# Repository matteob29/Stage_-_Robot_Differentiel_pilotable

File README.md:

# Stage - Robot Différentiel pilotable

Projet réalisé dans le cadre du **Stage de Première année**

**Ateliers destinés aux stagiaires de seconde**  
**ENSEIRB-MATMECA – CEA** 

**Auteurs :**  
Mattéo BINET  
Bastien TRAN-RUESCHE 

**Encadrant :**  
Thierry TARIS

**Date :** Juin 2025  

---

## Présentation générale

Cet atelier a été conçu dans le cadre du partenariat entre **l’ENSEIRB-MATMECA** et le **CEA**, dans le but d’initier des élèves de seconde aux bases de la robotique.  
Il s’est déroulé à **EirLab**, le fablab de l’enseirb, sur des séances de trois heures encadrées par des étudiants de première année.

L’objectif était de faire découvrir la démarche complète de conception d’un système embarqué à travers la réalisation d’un **robot différentiel pilotable**.  
L’atelier combine ainsi trois volets :  
1. la **découverte du robot et de ses composants** ;  
2. la **fabrication partielle du châssis** et l’assemblage ;  
3. la **programmation du comportement autonome** du robot.

---

## Le robot

Le robot conçu est un **modèle différentiel** à deux roues motrices et une roue folle.  
Chaque moteur est commandé indépendamment à l’aide d’un **driver L298**, piloté par un **microcontrôleur ESP32** programmé dans l’environnement Arduino.  
L’ensemble est relié par une **carte d’interconnexion** assurant la distribution de l’alimentation et des signaux de commande.

Les principaux éléments du système sont :
- ESP32 (microcontrôleur)  
- Driver moteur L298  
- Deux moteurs à courant continu  
- Capteur à ultrasons  
- LEDs et interrupteurs  
- Batterie d’alimentation  

Le robot peut se déplacer, s’arrêter en fonction de la détection d’obstacles et être commandé à distance via une interface sans fil.

---

## Déroulement de l’atelier

L’atelier débute par une présentation du principe du robot différentiel et de ses composants électroniques.  
Les élèves réalisent ensuite la **plaque inférieure du châssis** à l’aide d’une **découpeuse laser**, puis procèdent à l’assemblage mécanique et à la soudure des moteurs.

La seconde partie est consacrée à la **programmation**.  
À partir d’un code partiellement fourni, les élèves complètent la logique du comportement autonome du robot à l’aide de fonctions simples issues d’une bibliothèque dédiée (`pami_lib.h`).

Exemples de fonctions utilisées :
- `avancer()`, `reculer()`, `stop()` : contrôle du déplacement  
- `mesurerDistance()` : lecture du capteur à ultrasons  
- `bluetoothControl()` : pilotage sans fil  

L’objectif final est d’obtenir un robot capable d’avancer, de s’arrêter en présence d’un obstacle et, en bonus, d’effectuer une manœuvre d’évitement.

---

## Objectifs pédagogiques

- Introduire les bases de la **robotique mobile** et des systèmes embarqués.  
- Apprendre à **assembler** et **câbler** un système électronique simple.  
- Découvrir la **programmation en C/Arduino** appliquée au pilotage de moteurs.  
- Développer des compétences de **rigueur, logique et travail collaboratif**.  

---

## Conclusion

Cet atelier illustre de manière concrète le processus complet de conception d’un système robotique :  
de la modélisation mécanique à la programmation, en passant par l’assemblage électronique.  
Il permet aux élèves de seconde d’aborder de façon pratique les disciplines de l’ingénierie et de découvrir le fonctionnement d’un robot autonome.

---

## Contenu du dépôt GitHub

Le dépôt [Stage - Robot Différentiel pilotable](https://github.com/matteob29/Stage_-_Robot_Differentiel_pilotable) contient les éléments suivants :

- [Codes/](./Codes)                        → Programmes ESP32 avec les controlles Wifi ou manette de PS4
- [Datasheets/](./Datasheets)                → Datasheet des coomposants utilisés
- [Images/](./Images)                      → Illustrations, photos et rendus du robot
- [Meca/](./Meca)                          → Modèles 3D et plans mécaniques (SolidWorks, SVG)
- [PCB/](./PCB)                            → Layouts et typons
- [Rapports/](./Rapports)                    → Rapports de stage et documents de présentation
- [README.md](./README.md)
  
---

© 2025 — Mattéo BINET, Bastien TRAN-RUESCHE  
Département Électronique — Stage 1ère année  
Enseirb-Matmeca — Robot Différentiel pilotable

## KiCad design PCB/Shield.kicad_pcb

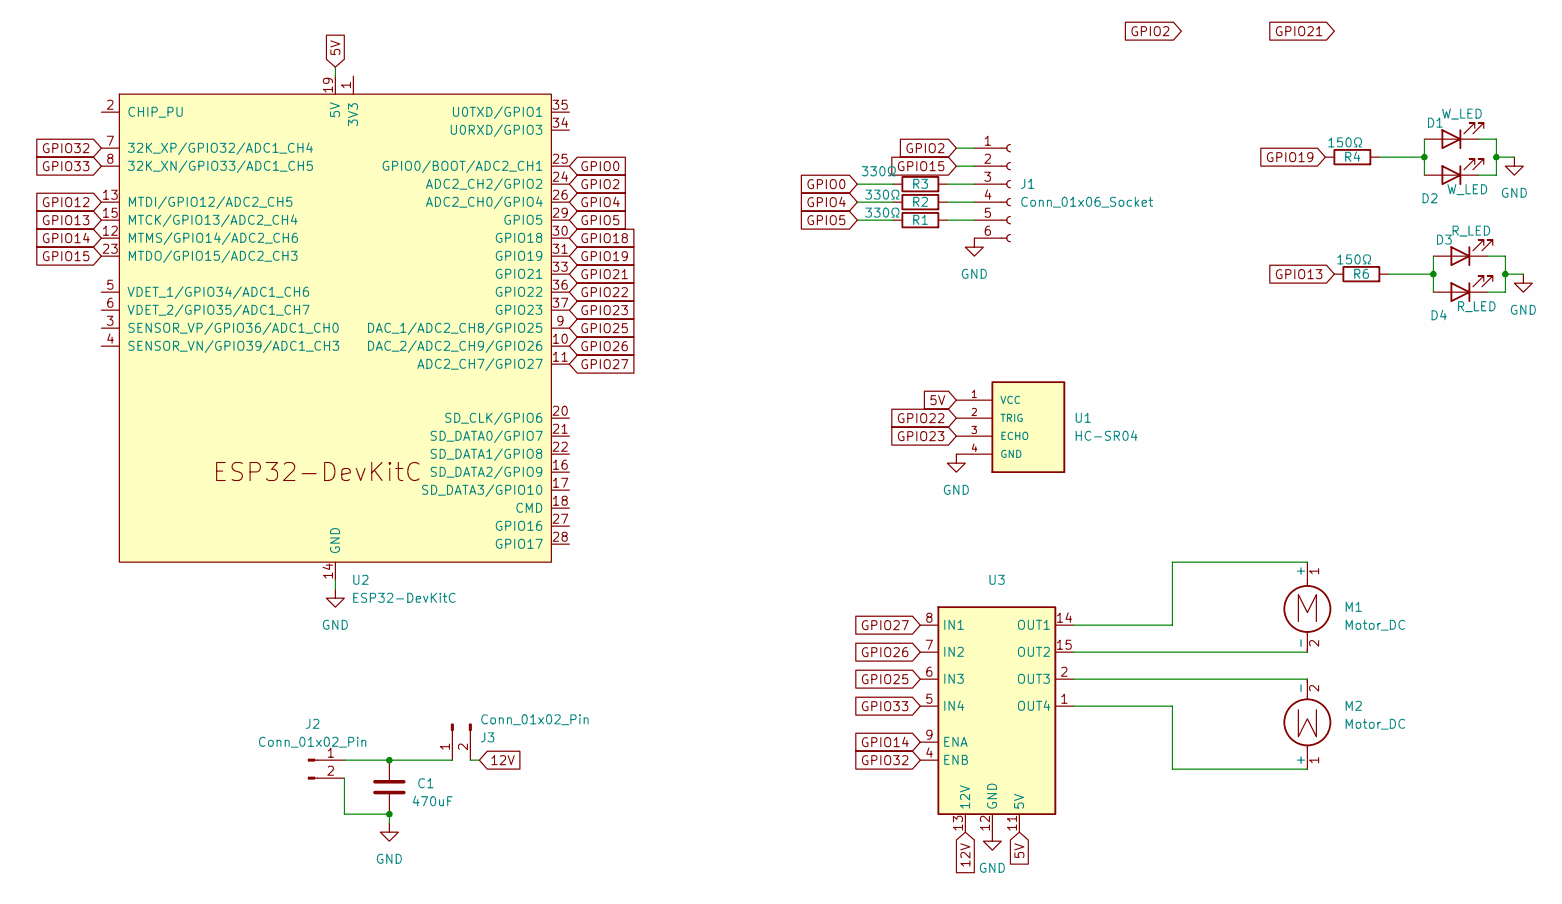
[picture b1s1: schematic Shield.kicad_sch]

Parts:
C1: 470uF; C_Axial_L3.8mm_D2.6mm_P7.50mm_Horizontal
D1, D2: W_LED; LED_D5.0mm_Horizontal_O6.35mm_Z3.0mm
D3, D4: R_LED; LED_D5.0mm_Horizontal_O6.35mm_Z3.0mm
J1: Conn_01x06_Socket; JST_XH_B6B-XH-A_1x06_P2.50mm_Vertical
J2: Conn_01x02_Pin; PinHeader_1x02_P2.54mm_Vertical
J3: Conn_01x02_Pin; JST_PH_B2B-PH-K_1x02_P2.00mm_Vertical
M1, M2: Motor_DC; Pad_Motor_DC_CMS
R1, R2, R3: 330Ω; R_Axial_DIN0207_L6.3mm_D2.5mm_P10.16mm_Horizontal
R4, R6: 150Ω; R_Axial_DIN0207_L6.3mm_D2.5mm_P10.16mm_Horizontal
U1: HC-SR04; XCVR_HC-SR04
U2: ESP32-DevKitC
U3: Driver_Motor_L298N

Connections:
5V: U1.1 (VCC), U2.19 (5V), U3.11 (5V)
12V: J3.2, U3.13 (12V)
GND: C1.2, D1.1 (K), D2.1 (K), D3.1 (K), D4.1 (K), J1.6, J2.2, U1.4 (GND), U2.14 (GND), U2.32 (GND), U2.38 (GND), U3.12 (GND)
GPIO0: R3.1, U2.25 (GPIO0/BOOT/ADC2_CH1)
GPIO2: J1.1, U2.24 (ADC2_CH2/GPIO2)
GPIO4: R2.1, U2.26 (ADC2_CH0/GPIO4)
GPIO5: R1.1, U2.29 (GPIO5)
GPIO12: U2.13 (MTDI/GPIO12/ADC2_CH5)
GPIO13: R6.1, U2.15 (MTCK/GPIO13/ADC2_CH4)
GPIO14: U2.12 (MTMS/GPIO14/ADC2_CH6), U3.9 (ENA)
GPIO15: J1.2, U2.23 (MTDO/GPIO15/ADC2_CH3)
GPIO18: U2.30 (GPIO18)
GPIO19: R4.1, U2.31 (GPIO19)
GPIO21: U2.33 (GPIO21)
GPIO22: U1.2 (TRIG), U2.36 (GPIO22)
GPIO23: U1.3 (ECHO), U2.37 (GPIO23)
GPIO25: U2.9 (DAC_1/ADC2_CH8/GPIO25), U3.6 (IN3)
GPIO26: U2.10 (DAC_2/ADC2_CH9/GPIO26), U3.7 (IN2)
GPIO27: U2.11 (ADC2_CH7/GPIO27), U3.8 (IN1)
GPIO32: U2.7 (32K_XP/GPIO32/ADC1_CH4), U3.4 (ENB)
GPIO33: U2.8 (32K_XN/GPIO33/ADC1_CH5), U3.5 (IN4)
unnamed: D1.2 (A), D2.2 (A), R4.2
unnamed: D3.2 (A), D4.2 (A), R6.2
unnamed: J1.3, R3.2
unnamed: J1.4, R2.2
unnamed: J1.5, R1.2
unnamed: C1.1, J2.1, J3.1
unnamed: M1.1 (+), U3.14 (OUT1)
unnamed: M1.2 (-), U3.15 (OUT2)
unnamed: M2.1 (+), U3.1 (OUT4)
unnamed: M2.2 (-), U3.2 (OUT3)

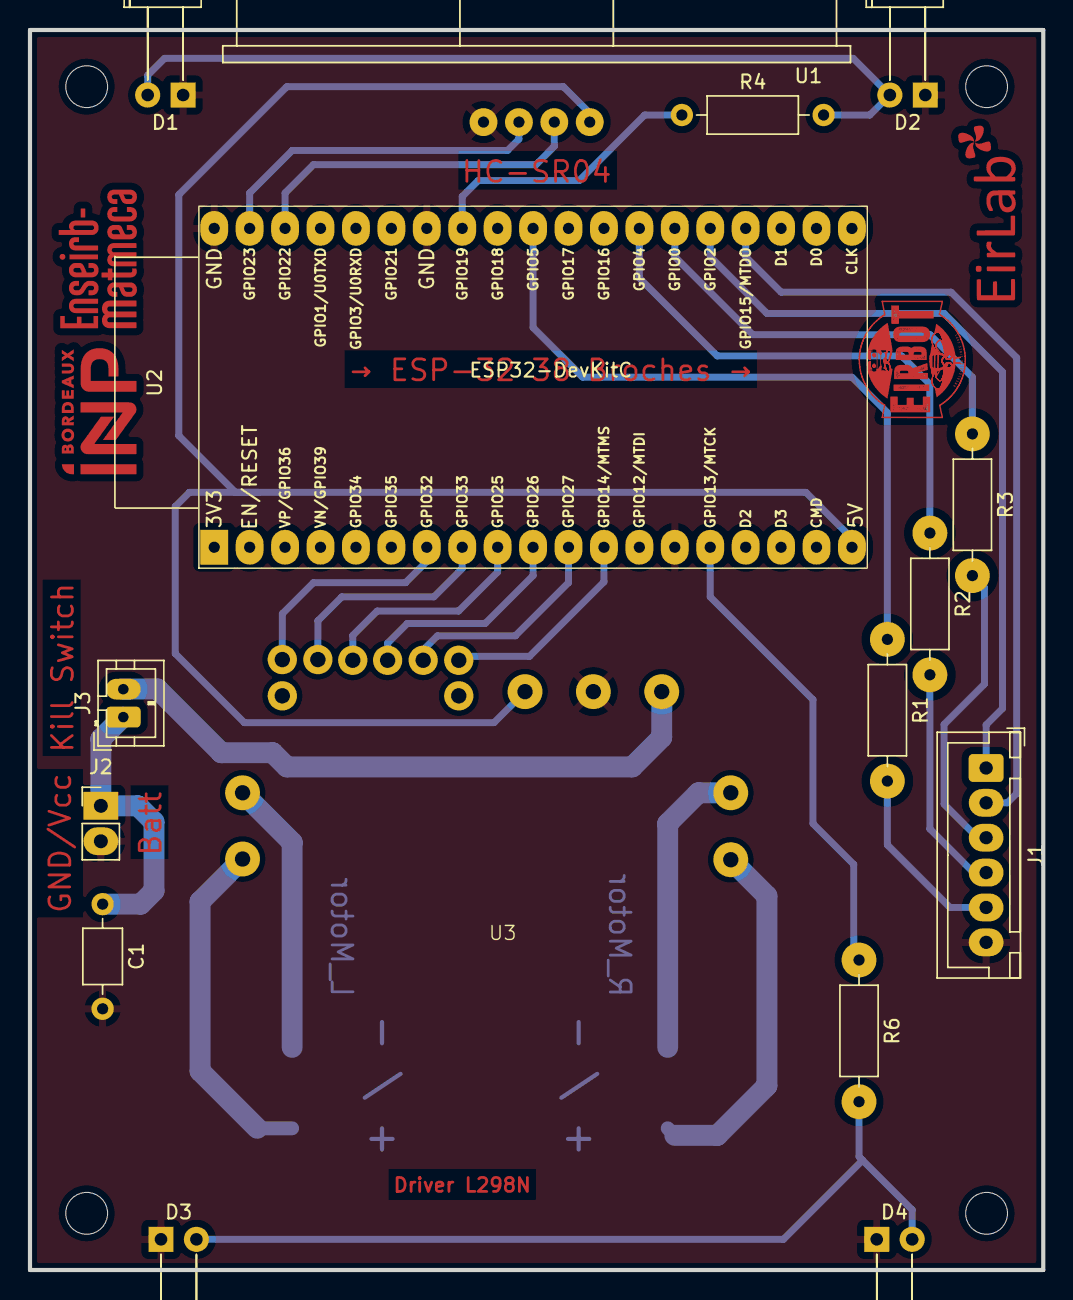
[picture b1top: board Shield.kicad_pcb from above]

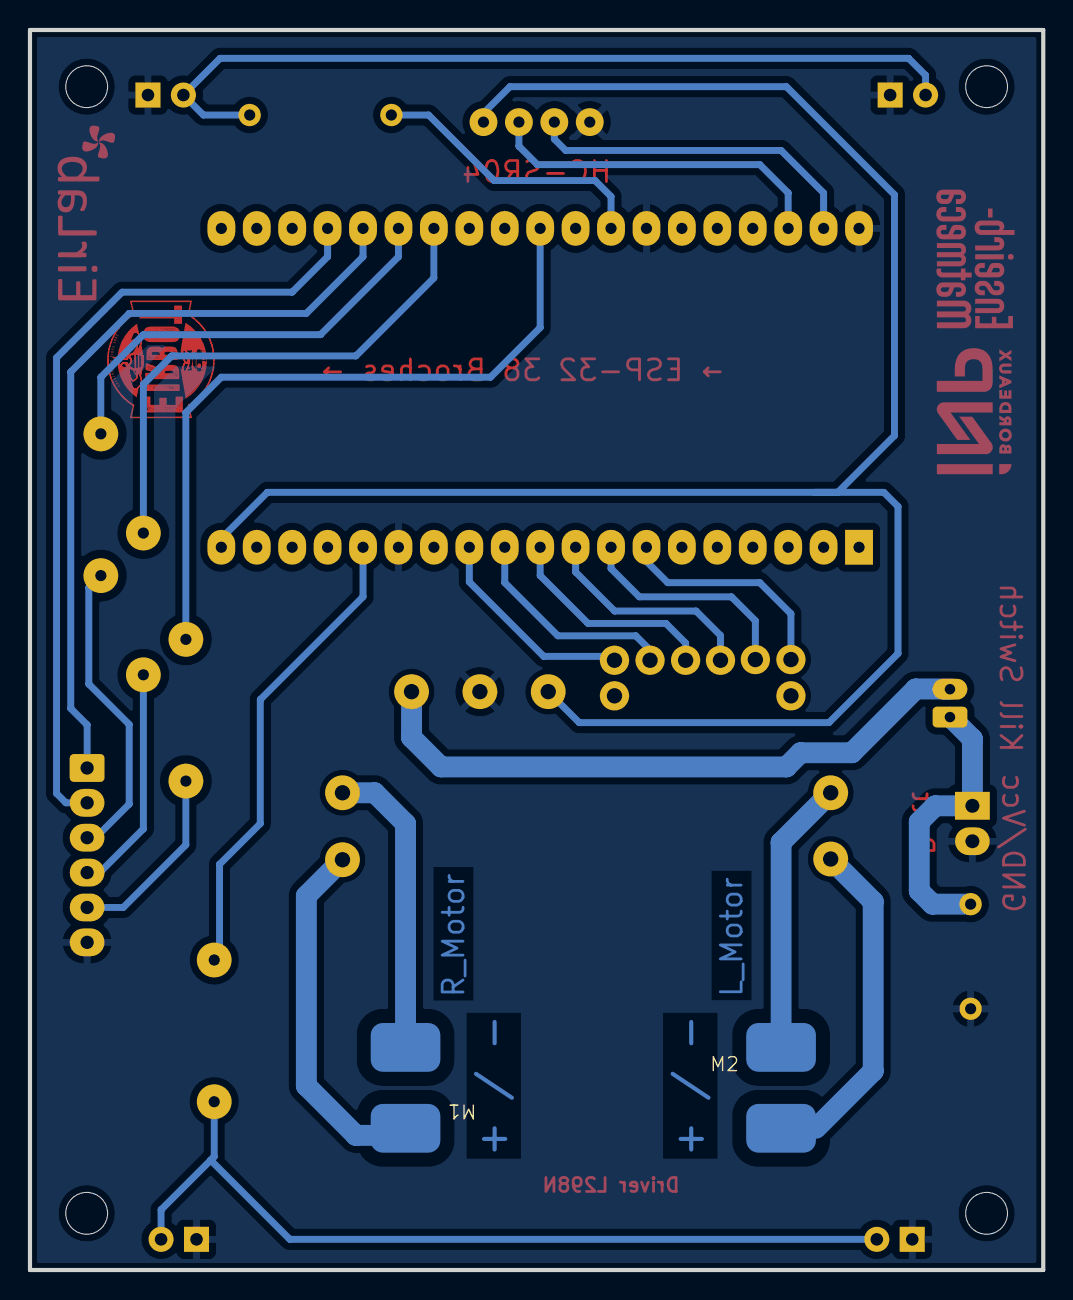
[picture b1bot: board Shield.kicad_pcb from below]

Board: 2 copper layers, 72.6 x 88.9 mm, 18 parts (2 on the bottom side), 28 nets.

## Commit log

2025-10-29 Ajout ./Meca
2025-10-29 Ajout fichier du PCB_shield
2025-10-29 Revise README for project details and objectives
    Updated the README to provide detailed project information, objectives, and contents of the GitHub repository.
